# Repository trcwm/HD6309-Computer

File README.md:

# HD6309-Computer
A computer based on the HD6309 CPU, done for the Retro Challenge 2017/04.

Read the blog: [https://namoseley.wordpress.com/category/retrochallenge/](https://namoseley.wordpress.com/category/retrochallenge/)

Features:
* HD6309 CPU
	* Binary compatible to MC6809
	* ..but faster instruction execution,
	* ..extended registers,
	* ..additional instructions,
	* and lots more!
* 1MB of RAM:
    * mapped in 32K pages at 0x0000 .. 0x7FFF
    * fixed page at 0x8000 .. 0xDFFF
* 2KB of IO space:
    * SC16C550B UART at 0xE000
    * 8-bit expansions port at 0xE010(untested!)
* Memory map register:
    * 5-bit entry sets A15..A19 on RAM
    * reg at address 0xE800
* 4KB of ROM:
    * Memory check
    * SREC loader

Licence: CERN Open Hardware Licence v1.2

Development time provided by: http://www.moseleyinstruments.com

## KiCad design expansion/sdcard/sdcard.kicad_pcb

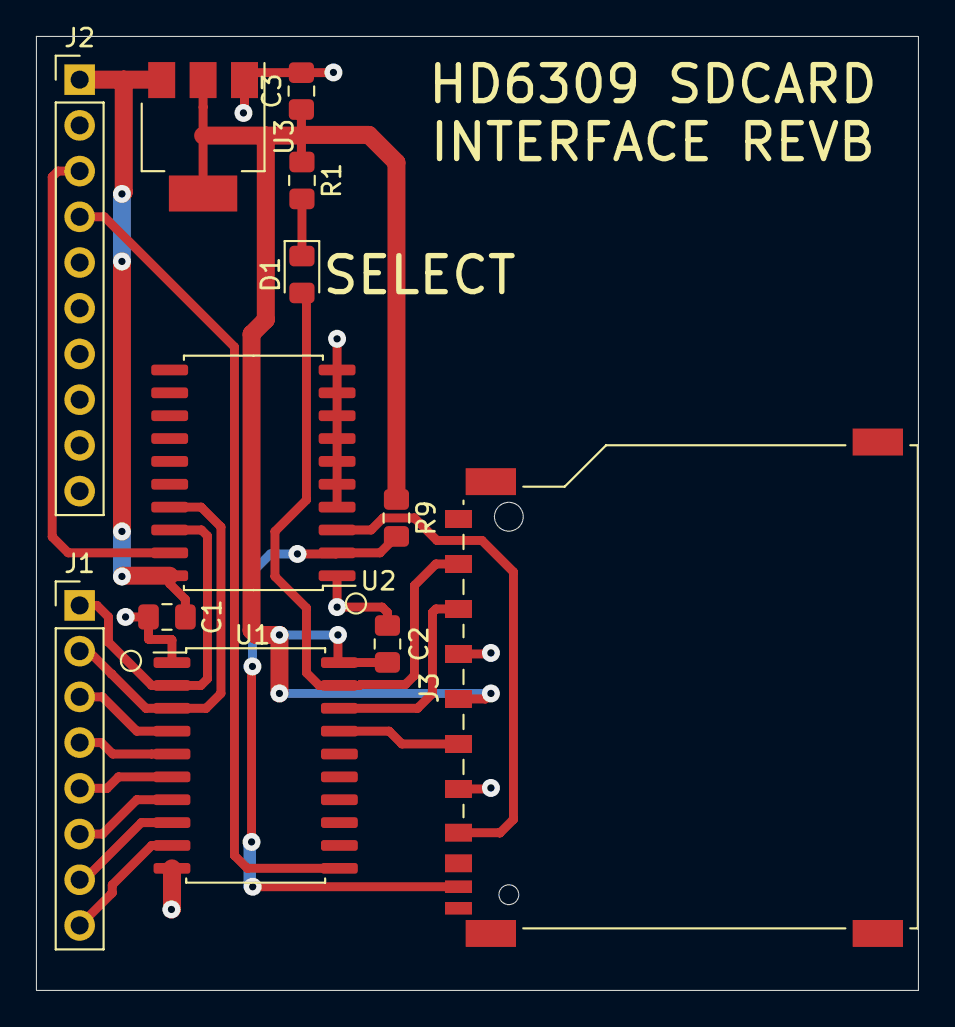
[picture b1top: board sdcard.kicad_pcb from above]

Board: 2 copper layers, 49.0 x 53.0 mm, 12 parts (0 on the bottom side), 19 nets.

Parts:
C1, C2, C3: 100n; C_0805_2012Metric_Pad1.15x1.40mm_HandSolder
D1: LED_Small; LED_0805_2012Metric_Pad1.15x1.40mm_HandSolder
J1: Conn_01x08; PinHeader_1x08_P2.54mm_Vertical
J2: Conn_01x10; PinHeader_1x10_P2.54mm_Vertical
J3: SD_Card; SD_TE_2041021
R1: 470; R_0805_2012Metric_Pad1.15x1.40mm_HandSolder
R9: 10k; R_0805_2012Metric_Pad1.15x1.40mm_HandSolder
U1: 74LVX574; SOIC-20W_7.5x12.8mm_P1.27mm
U2: 74HCT541; SOIC-20W_7.5x12.8mm_P1.27mm
U3: LM1117-3.3; SOT-223-3_TabPin2

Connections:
+3V3: C2.1, C3.1, J3.4, R1.1, R9.1, U1.20, U3.2
+5V: C1.1, J2.1, U2.20, U3.3
CARD_DETECT: J3.10, R9.2, U2.2
GND: C1.2, C2.2, C3.2, J2.2, J3.3, J3.6, U1.1, U1.10, U2.1, U2.4, U2.5, U2.6, U2.7, U2.8, U2.9, U2.10, U3.1
MISO: J3.7, U2.3
MOSI_3V: J3.2, U1.18
unnamed: D1.1, R1.2
unnamed: J1.1, U1.2, U2.18
unnamed: J1.2, U1.3, U2.17
unnamed: J1.3, U1.4
unnamed: J1.4, U1.5
unnamed: J1.5, U1.6
unnamed: J1.6, U1.7
unnamed: J1.7, U1.8
unnamed: J1.8, U1.9
SCK_3V: J3.5, U1.17
~RD: J2.3, U2.19
~SS_3V: D1.2, J3.1, U1.19
~WR: J2.4, U1.11

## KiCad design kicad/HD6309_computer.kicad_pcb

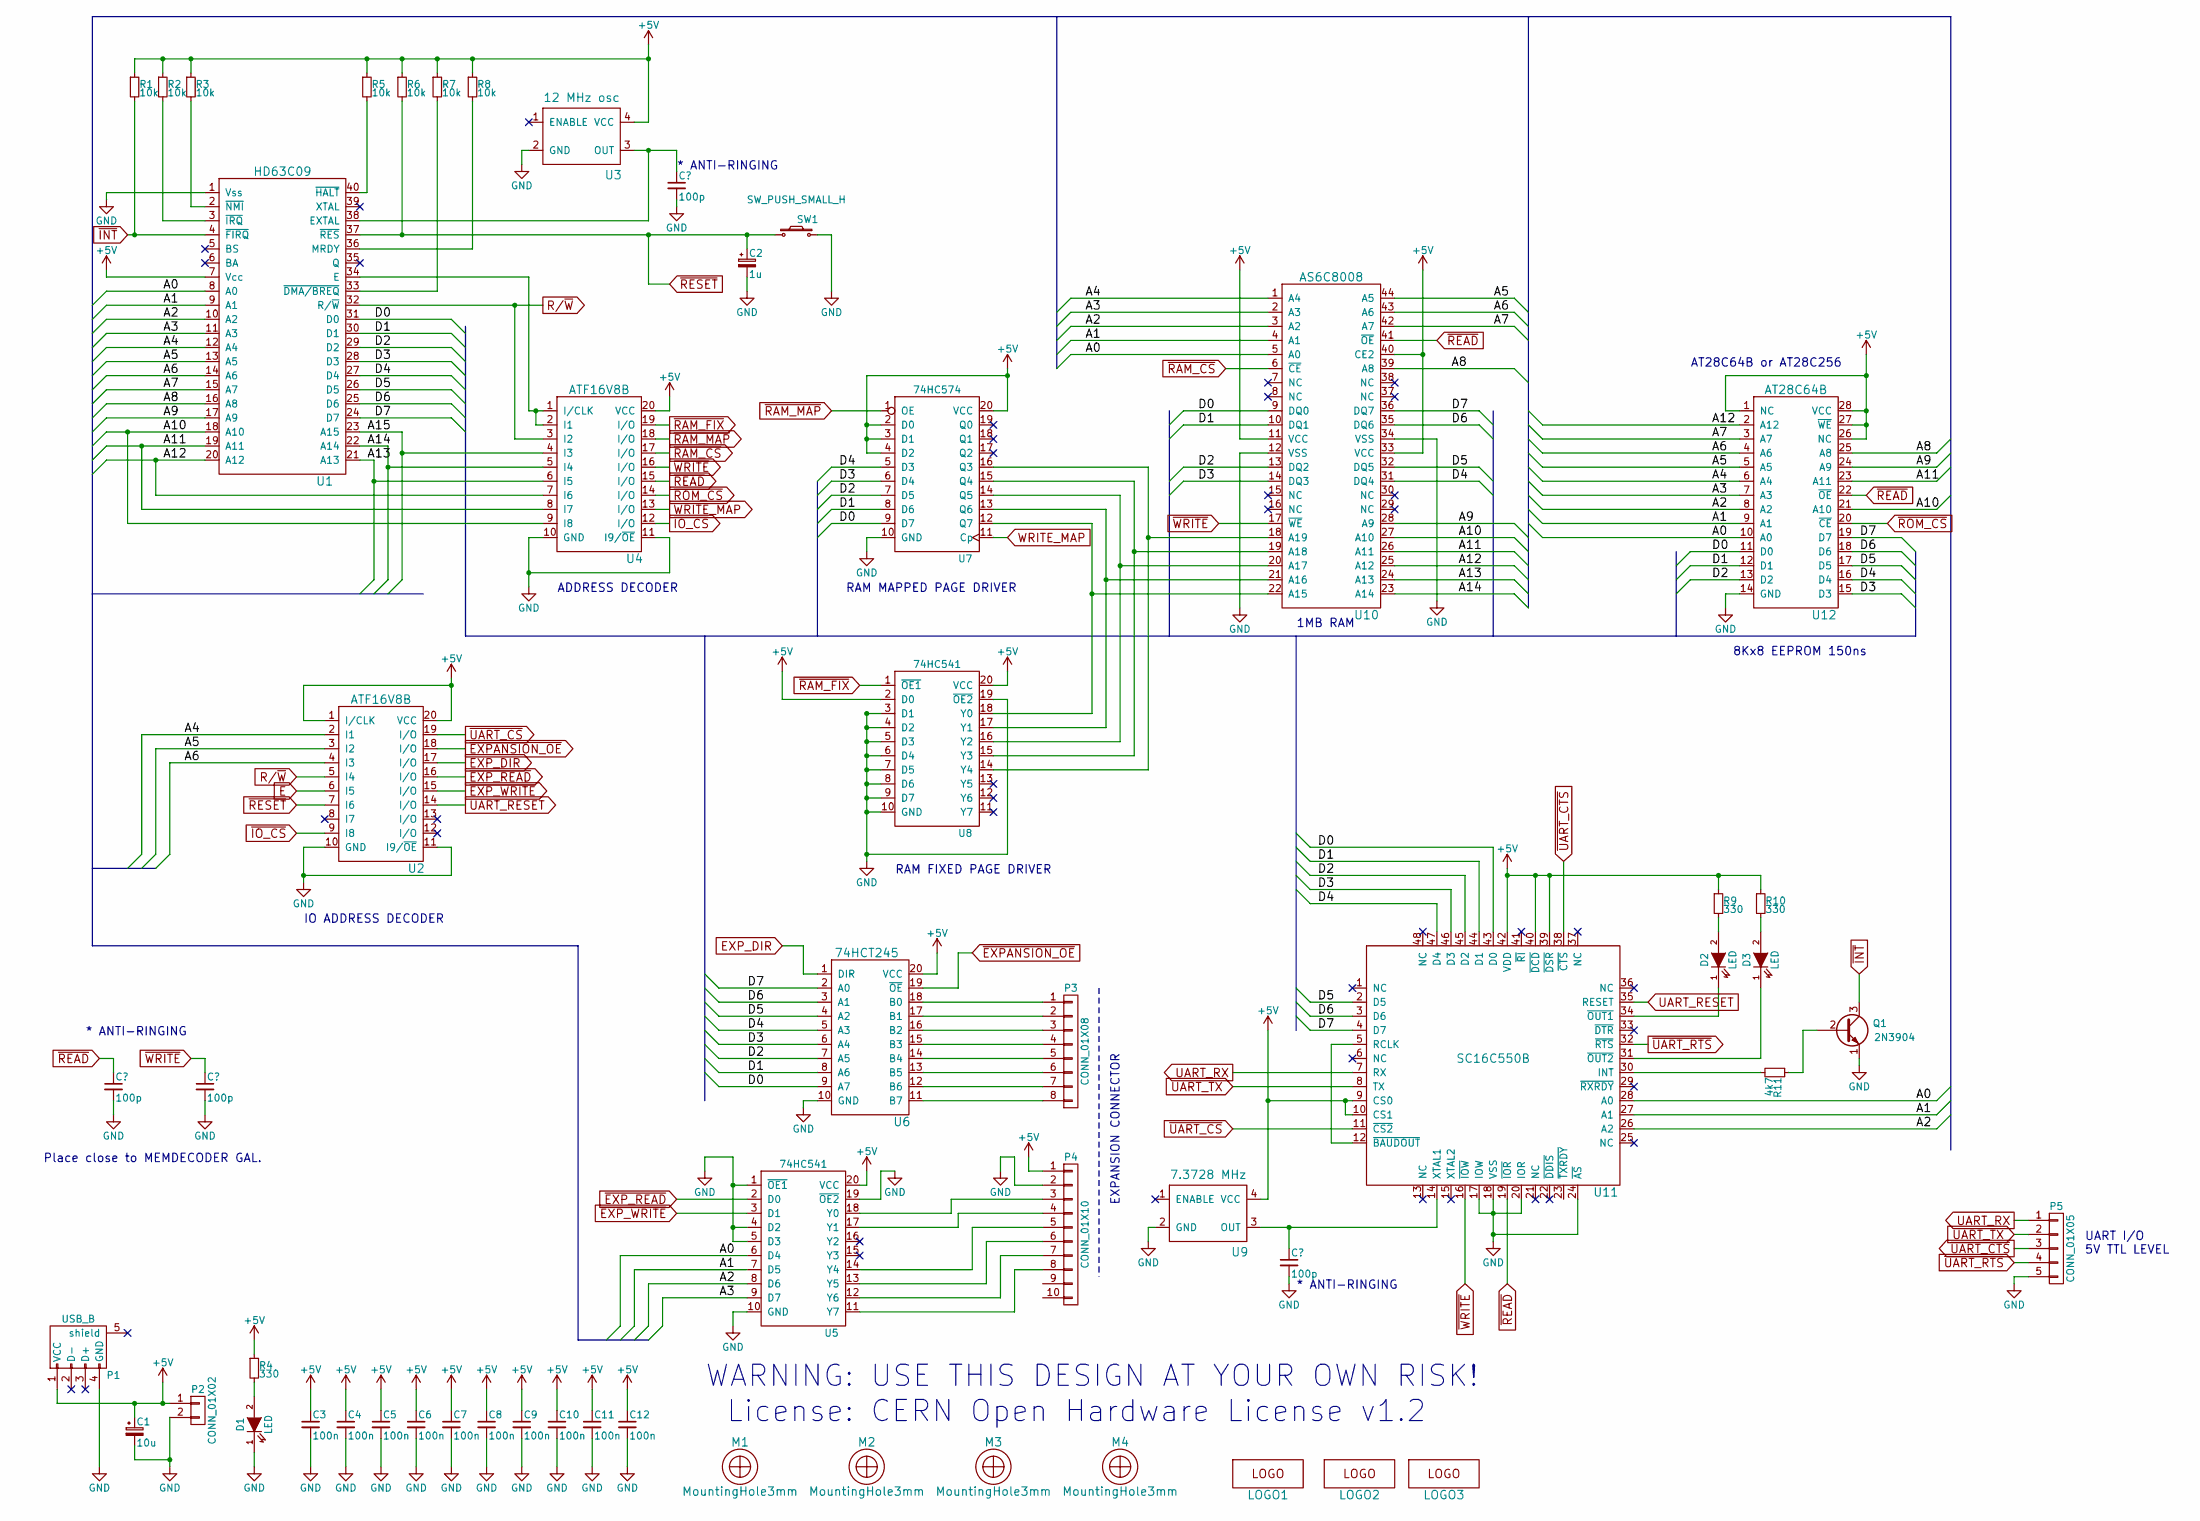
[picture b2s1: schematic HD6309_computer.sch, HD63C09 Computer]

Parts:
C1: 10u; CP_Elec_6.3x5.3
C2: 1u; CP_Elec_6.3x5.3
C3, C4, C5, C6, C7, C8, C9, C10, C11, C12: 100n; C_0805_HandSoldering
D1, D2, D3: LED; LED_D3.0mm_centered
LOGO1: Logo; moseley_instruments_logo_smaller
LOGO2: Logo; retro_challenge_logo
LOGO3: Logo; HD6309_computer_name
M1, M2, M3, M4: MountingHole3mm; MountingHole_3.2mm_M3_DIN965
P1: USB_B
P2: CONN_01X02; Pin_Header_Straight_1x02_Pitch2.54mm
P3: CONN_01X08; Pin_Header_Straight_1x08_Pitch2.54mm
P4: CONN_01X10; Pin_Header_Straight_1x10_Pitch2.54mm
P5: CONN_01X05; Pin_Header_Straight_1x05_Pitch2.54mm
Q1: 2N3904; TO-92_Inline_Wide
R1, R2, R3, R5, R6, R7, R8: 10k; R_0805_HandSoldering
R4, R9, R10: 330; R_0805_HandSoldering
R11: 4k7; R_0805_HandSoldering
SW1: SW_PUSH_SMALL_H; SW_PUSH_6mm
U1: HD63C09; DIP-40_W15.24mm_LongPads
U2, U4: ATF16V8B; DIP-20_W7.62mm_LongPads
U3: 12 MHz osc; OSCSMD7x5
U5, U8: 74HC541; SOIC-20W_7.5x12.8mm_Pitch1.27mm
U6: 74HCT245; SOIC-20W_7.5x12.8mm_Pitch1.27mm
U7: 74HC574; SOIC-20W_7.5x12.8mm_Pitch1.27mm
U9: 7.3728 MHz; OSCSMD7x5
U10: AS6C8008; TSOP-II_44pin_W400mil
U11: SC16C550B; LQFP-48_7x7mm_Pitch0.5mm
U12: AT28C64B; DIP-28_W15.24mm_LongPads

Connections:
/A0: U1.8 (A0), U5.6 (D4), U10.5 (A0), U11.28 (A0), U12.10 (A0)
/A1: U1.9 (A1), U5.7 (D5), U10.4 (A1), U11.27 (A1), U12.9 (A1)
/A2: U1.10 (A2), U5.8 (D6), U10.3 (A2), U11.26 (A2), U12.8 (A2)
/A3: U1.11 (A3), U5.9 (D7), U10.2 (A3), U12.7 (A3)
/A4: U1.12 (A4), U2.2 (I1), U10.1 (A4), U12.6 (A4)
/A5: U1.13 (A5), U2.3 (I2), U10.44 (A5), U12.5 (A5)
/A6: U1.14 (A6), U2.4 (I3), U10.43 (A6), U12.4 (A6)
/A7: U1.15 (A7), U10.42 (A7), U12.3 (A7)
/A8: U1.16 (A8), U10.39 (A8), U12.25 (A8)
/A9: U1.17 (A9), U10.28 (A9), U12.24 (A9)
/A10: U1.18 (A10), U4.9 (I8), U10.27 (A10), U12.21 (A10)
/A11: U1.19 (A11), U4.8 (I7), U10.26 (A11), U12.23 (A11)
/A12: U1.20 (A12), U4.7 (I6), U10.25 (A12), U12.2 (A12)
/A13: U1.21 (A13), U4.6 (I5), U10.24 (A13)
/A14: U1.22 (A14), U4.5 (I4), U10.23 (A14)
/A15: U1.23 (A15), U4.4 (I3)
/D0: U1.31 (D0), U6.9 (A7), U7.9 (D7), U10.9 (DQ0), U11.43 (D0), U12.11 (D0)
/D1: U1.30 (D1), U6.8 (A6), U7.8 (D6), U10.10 (DQ1), U11.44 (D1), U12.12 (D1)
/D2: U1.29 (D2), U6.7 (A5), U7.7 (D5), U10.13 (DQ2), U11.45 (D2), U12.13 (D2)
/D3: U1.28 (D3), U6.6 (A4), U7.6 (D4), U10.14 (DQ3), U11.46 (D3), U12.15 (D3)
/D4: U1.27 (D4), U6.5 (A3), U7.5 (D3), U10.31 (DQ4), U11.47 (D4), U12.16 (D4)
/D5: U1.26 (D5), U6.4 (A2), U10.32 (DQ5), U11.2 (D5), U12.17 (D5)
/D6: U1.25 (D6), U6.3 (A1), U10.35 (DQ6), U11.3 (D6), U12.18 (D6)
/D7: U1.24 (D7), U6.2 (A0), U10.36 (DQ7), U11.4 (D7), U12.19 (D7)
EXP_DIR: U2.17 (I/O), U6.1 (DIR)
unnamed: D1.2 (A), R4.2
unnamed: D2.1 (K), U11.34 (~OUT1)
unnamed: D2.2 (A), R9.2
unnamed: D3.1 (K), U11.31 (~OUT2)
unnamed: D3.2 (A), R10.2
unnamed: P3.1, U6.18 (B0)
unnamed: P3.2, U6.17 (B1)
unnamed: P3.3, U6.16 (B2)
unnamed: P3.4, U6.15 (B3)
unnamed: P3.5, U6.14 (B4)
unnamed: P3.6, U6.13 (B5)
unnamed: P3.7, U6.12 (B6)
unnamed: P3.8, U6.11 (B7)
unnamed: P4.3, U5.18 (Y0)
unnamed: P4.4, U5.17 (Y1)
unnamed: P4.5, U5.14 (Y4)
unnamed: P4.6, U5.13 (Y5)
unnamed: P4.7, U5.12 (Y6)
unnamed: P4.8, U5.11 (Y7)
unnamed: Q1.2 (B), R11.1
unnamed: R2.2, U1.3 (~IRQ)
unnamed: R3.2, U1.2 (~NMI)
unnamed: R5.2, U1.40 (~HALT)
unnamed: R7.2, U1.33 (~DMA/BREQ)
unnamed: R8.2, U1.36 (MRDY)
unnamed: R11.2, U11.30 (INT)
unnamed: U1.34 (E), U4.1 (I/CLK), U4.2 (I1)
unnamed: U1.38 (EXTAL), U3.3 (OUT)
unnamed: U7.16 (Q3), U8.14 (Y4), U10.18 (A19)
unnamed: U7.15 (Q4), U8.15 (Y3), U10.19 (A18)
unnamed: U7.14 (Q5), U8.16 (Y2), U10.20 (A17)
unnamed: U7.13 (Q6), U8.17 (Y1), U10.21 (A16)
unnamed: U7.12 (Q7), U8.18 (Y0), U10.22 (A15)
unnamed: U11.5 (RCLK), U11.12 (~BAUDOUT)
unnamed: U9.3 (OUT), U11.14 (XTAL1)
R/~W: U1.32 (R/~W), U2.5 (I4), U4.3 (I2)
UART_RX: P5.1, U11.7 (RX)
UART_TX: P5.2, U11.8 (TX)
WRITE_MAP: U4.13 (I/O), U7.11 (Cp)
~EXPANSION_OE: U2.18 (I/O), U6.19 (~OE)
~EXP_READ: U2.16 (I/O), U5.2 (D0)
~EXP_WRITE: U2.15 (I/O), U5.3 (D1)
~INT: Q1.3 (C), R1.2, U1.4 (~FIRQ)
~IO_CS: U2.9 (I8), U4.12 (I/O)
~RAM_CS: U4.17 (I/O), U10.6 (~CE)
~RAM_FIX: U4.19 (I/O), U8.1 (~OE1)
~RAM_MAP: U4.18 (I/O), U7.1 (OE)
~READ: U4.15 (I/O), U10.41 (~OE), U11.19 (~IOR), U12.22 (~OE)
~ROM_CS: U4.14 (I/O), U12.20 (~CE)
~UART_CS: U2.19 (I/O), U11.11 (~CS2)
~UART_CTS: P5.3, U11.38 (~CTS)
~UART_RTS: P5.4, U11.32 (~RTS)
~WRITE: U4.16 (I/O), U10.17 (~WE), U11.16 (~IOW)

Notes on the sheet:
IO ADDRESS DECODER
RAM FIXED PAGE DRIVER
RAM MAPPED PAGE DRIVER
ADDRESS DECODER
1MB RAM
8Kx8 EEPROM 150ns
UART I/O 5V TTL LEVEL
EXPANSION CONNECTOR
* ANTI-RINGING
Place close to MEMDECODER GAL.
AT28C64B or AT28C256
License: CERN Open Hardware License v1.2
WARNING: USE THIS DESIGN AT YOUR OWN RISK!

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
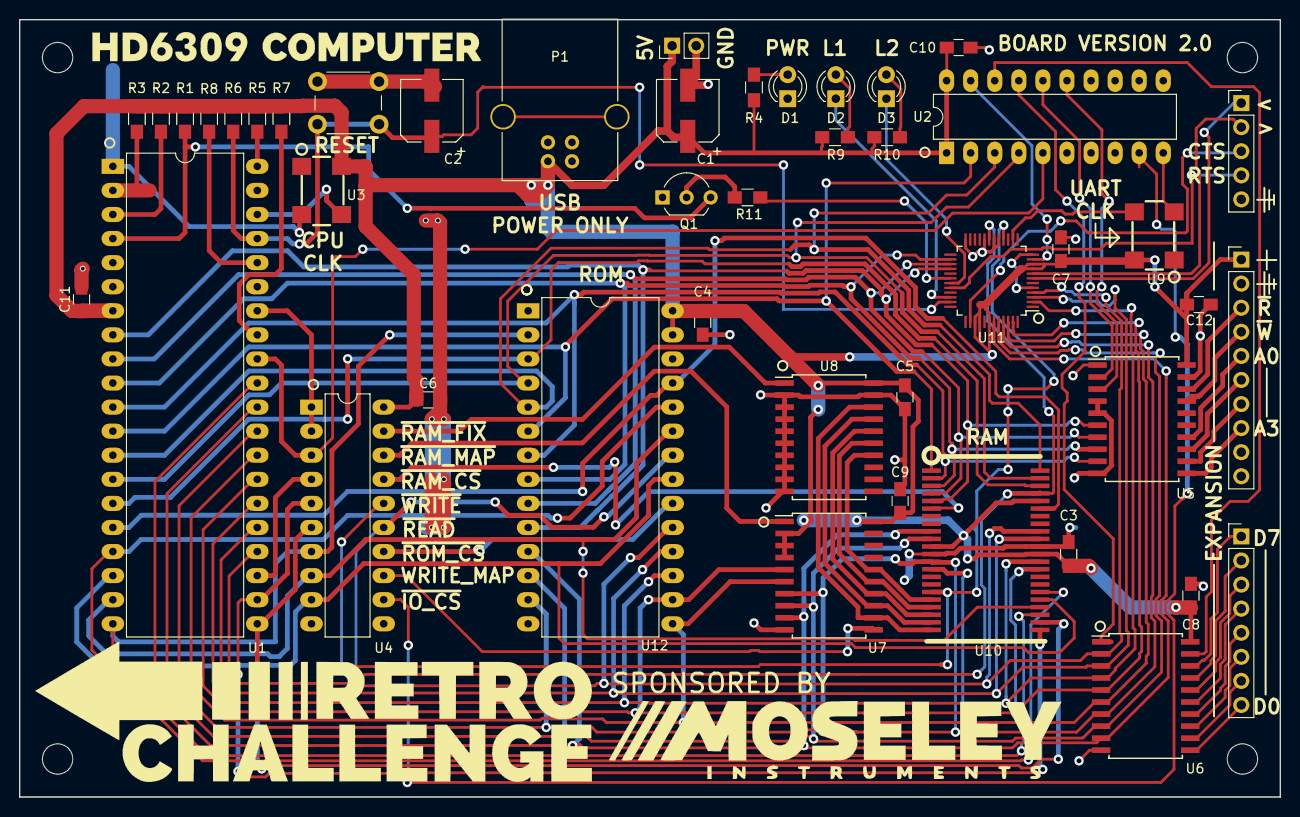
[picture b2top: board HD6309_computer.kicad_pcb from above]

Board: 2 copper layers, 133.0 x 82.0 mm, 52 parts (0 on the bottom side), 81 nets.

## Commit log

2017-05-07 HD6309 computer - first public commit.
2017-05-07 Typos.
2017-05-07 Added bootloader source code.
2017-05-07 Added ported Tiny Basic interpreter.
2017-05-07 Added a picture.
2017-05-07 Added animated gif, updated README.md
2017-05-07 hmm..
2017-05-07 Fixed typo.
2017-05-08 Added tiny basic documentation.
2019-09-30 Updated schematic with DRC fixes and TODOs
2019-10-01 Added test software to the HD6309 repo.
2019-10-06 Added v1 schematics as PDF for easier viewing
2019-10-06 Added expansion port test
2019-10-06 Fixed IO decoder GAL?
2019-10-06 Fixed IO Decoder.
2019-10-06 Added Kicad rescue libraries
2019-10-07 HD6309 SDCARD expansion.
2019-10-07 Updated exptest.asm
2019-10-11 SDCard expansion updated.
2019-10-22 Added test for SD card
2019-10-23 Can read SD card sector. Increased SD read speed
2019-10-23 Write sector works

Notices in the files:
kicad/HD6309_computer.sch:
Copyright Niels A. Moseley 2017
